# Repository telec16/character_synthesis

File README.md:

# Character Synthesis using Fourier Transform

Based on http://www.glensstuff.com/fouriersynthchargen/fouriersynthchargen.htm

## Front Panel

The front panel was made with Galva ( http://www.f5bu.fr/galva-download/ ), in French.

## Clock generation board

~/!\ DIVoddN is not synthetizable with Lattice LSE. I use Synplify Pro.~ Actually I don't know what's going on, but it does not correspond to the simulation. The hardware tests show no errors.

### FPGA pinmap

| Name 		| Pin Number | Pin Name | Location  |
|-----------|------------|----------|-----------|
| clk_1M2	| 13		 | PCLKT2_1	| X1.3		|
| clrn		| 14		 | PCLKC2_1	| J4.1		|
| clk_20k	| 8			 | CSSPIN	| J2.5		|
| clk_40k	| 9			 | MCLK		| J2.4		|
| clk_60k	| 10		 | SPISO	| J2.3		|
| clk_80k	| 11		 | PCLKT2_0	| J2.2		|
| clk_100k	| 12		 | PCLKC2_0	| J2.1		|
| E1A		| 16		 | SN		| SW1.1		|
| E1B		| 17		 | SPISI	| SW1.3		|
| E2A		| 20		 | PCLKC1_0	| SW2.1		|
| E2B		| 21		 | PCLKT1_0	| SW2.3		|
| blanking  | 5			 | PCLKC3_0	| J2.6		|
| led 		| 23		 | DONE		| D2		|
| pin1		| 28		 | SCL		| J2.8		|
| pin2		| 4			 | PCLKT3_0	| J2.7		|
| TDO		| 1			 | TDO		| J1.5		|
| TDI		| 32		 | TDI		| J1.3		|
| TCK		| 30		 | TCK		| J1.2		|
| TMS		| 29		 | TMS		| J1.1		|

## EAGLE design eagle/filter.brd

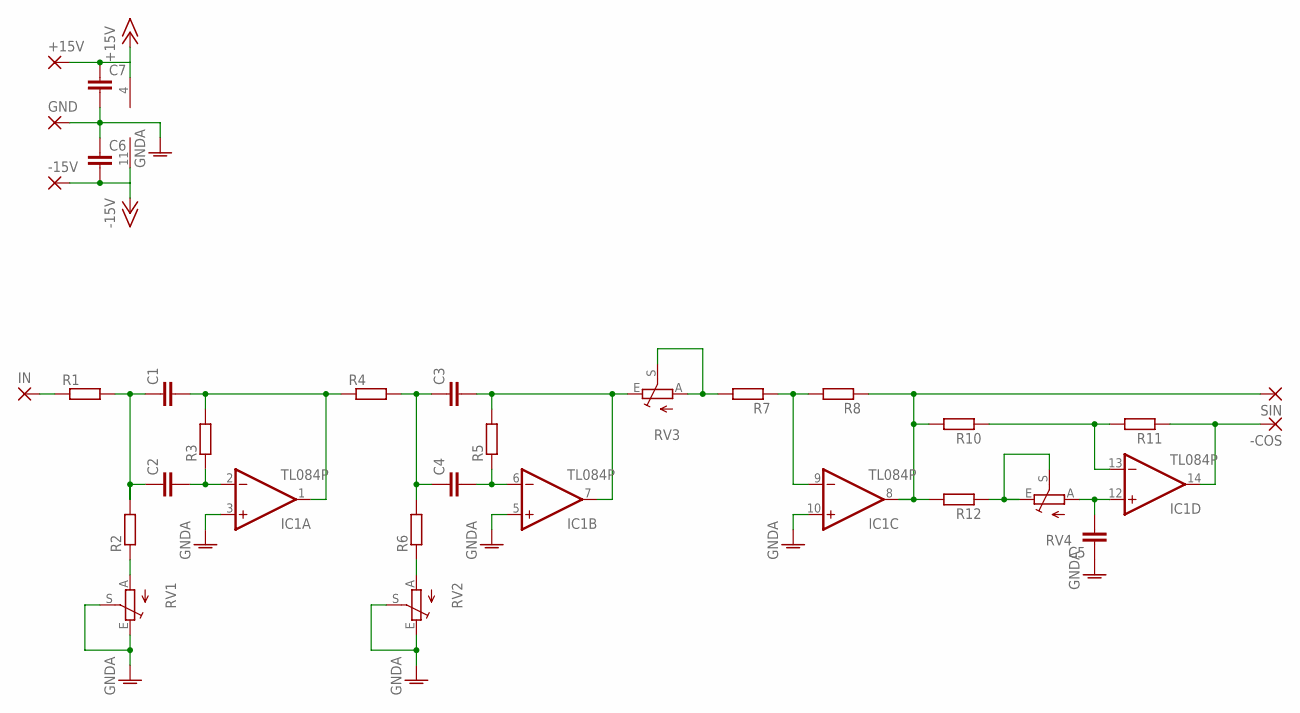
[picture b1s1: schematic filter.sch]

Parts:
+15V: 2,15/1,0
-15V: 2,15/1,0
-COS: 2,15/1,0
C1, C2, C3, C4, C5: C-EU025-025X050; C025-025X050
C6, C7: C-EU050-030X075; C050-030X075
GND: 2,15/1,0
IC1: TL084P; DIL14
IN: 2,15/1,0
R1, R2, R3, R4, R5, R6, R7, R8, R10, R11, R12: R-EU_0309/V; 0309V
RV1, RV2, RV3, RV4: TRIM_EU-RJ9W; RJ9W
SIN: 2,15/1,0

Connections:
+15V: +15V.1, C7.1, IC1.4 (V+)
-15V: -15V.1, C6.2, IC1.11 (V-)
GNDA: C5.1, C6.1, C7.2, GND.1, IC1.3 (+IN), IC1.5 (+IN), IC1.10 (+IN), RV1.E, RV1.S, RV2.E, RV2.S
unnamed: R2.1, RV1.A
unnamed: C1.1, C2.1, R1.2, R2.2
unnamed: -COS.1, IC1.14 (OUT), R11.1
unnamed: C1.2, IC1.1 (OUT), R3.2, R4.1
unnamed: C2.2, IC1.2 (-IN), R3.1
unnamed: IN.1, R1.1
unnamed: R6.1, RV2.A
unnamed: C3.1, C4.1, R4.2, R6.2
unnamed: C3.2, IC1.7 (OUT), R5.2, RV3.E
unnamed: C4.2, IC1.6 (-IN), R5.1
unnamed: R7.2, RV3.A, RV3.S
unnamed: IC1.9 (-IN), R7.1, R8.2
unnamed: IC1.8 (OUT), R8.1, R10.2, R12.2, SIN.1
unnamed: IC1.13 (-IN), R10.1, R11.2
unnamed: R12.1, RV4.E, RV4.S
unnamed: C5.2, IC1.12 (+IN), RV4.A

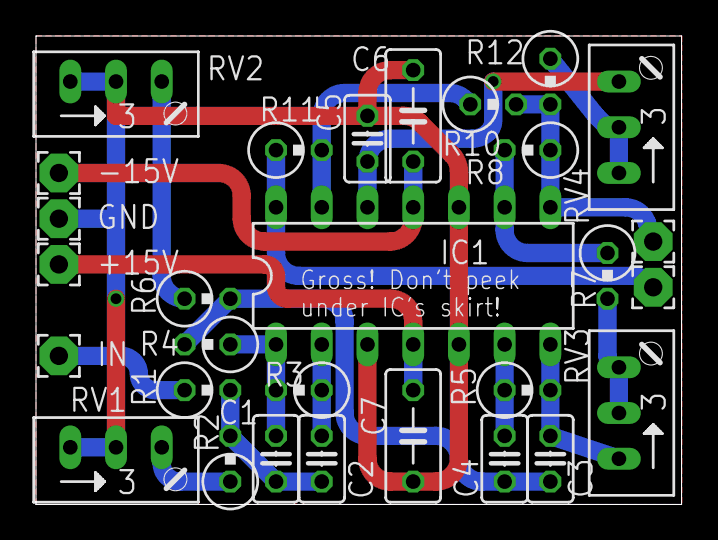
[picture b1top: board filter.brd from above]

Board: 2 copper layers, 35.9 x 26.0 mm, 29 parts (0 on the bottom side), 19 nets.

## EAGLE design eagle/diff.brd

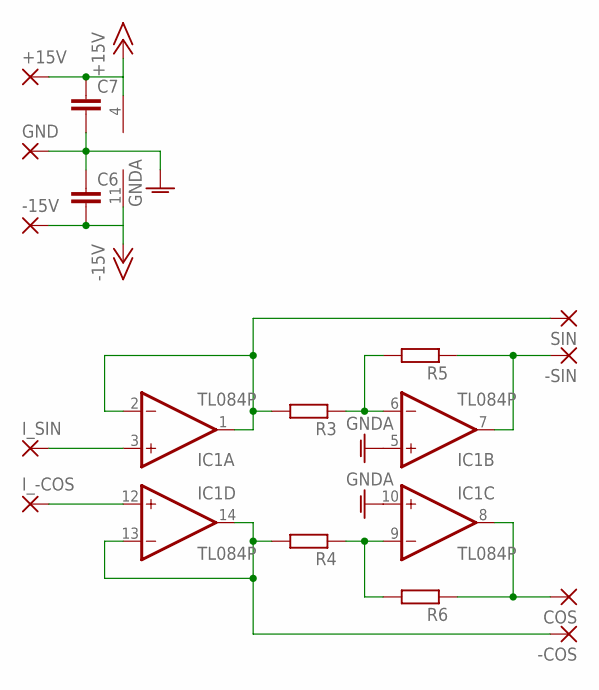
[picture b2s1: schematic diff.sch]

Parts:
+15V: 2,15/1,0
-15V: 2,15/1,0
-COS: 2,15/1,0
-SIN: 2,15/1,0
C6, C7: C-EU050-030X075; C050-030X075
COS: 2,15/1,0
GND: 2,15/1,0
IC1: TL084P; DIL14
I_-COS: 2,15/1,0
I_SIN: 2,15/1,0
R3, R4, R5, R6: R-EU_0309/V; 0309V
SIN: 2,15/1,0

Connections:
+15V: +15V.1, C7.1, IC1.4 (V+)
-15V: -15V.1, C6.2, IC1.11 (V-)
GNDA: C6.1, C7.2, GND.1, IC1.5 (+IN), IC1.10 (+IN)
unnamed: IC1.3 (+IN), I_SIN.1
unnamed: IC1.12 (+IN), I_-COS.1
unnamed: -COS.1, IC1.13 (-IN), IC1.14 (OUT), R4.2
unnamed: IC1.1 (OUT), IC1.2 (-IN), R3.2, SIN.1
unnamed: IC1.6 (-IN), R3.1, R5.2
unnamed: -SIN.1, IC1.7 (OUT), R5.1
unnamed: IC1.9 (-IN), R4.1, R6.2
unnamed: COS.1, IC1.8 (OUT), R6.1

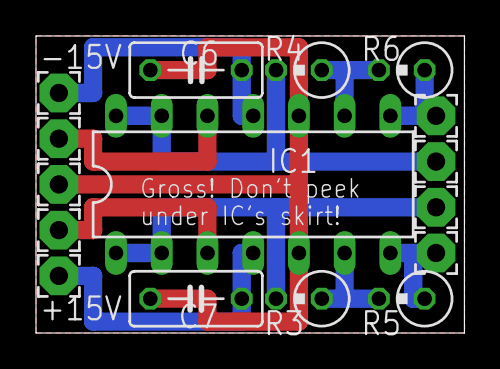
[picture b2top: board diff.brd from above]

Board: 2 copper layers, 23.8 x 16.5 mm, 16 parts (0 on the bottom side), 11 nets.

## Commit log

2020-01-24 schematics
2020-01-26 Kicad files for the clocks source
2020-01-26 Lattice files for clocks gen
2020-02-08 Finished PCB
2020-02-08 ltspice files
2020-05-23 clock gen Minimal Working Example (tested)
2020-05-23 Changed to Synplify
2020-05-23 Added front panel files
2020-05-23 Encoder structure
2020-05-25 Changed div files to produce good signals. Tested.
2020-05-25 Finished design, tests to be done
